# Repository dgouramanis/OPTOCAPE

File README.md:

Photocoupler cape for BeagleBone Black with integrated video serializer

https://youtu.be/7uQYPXgA6WU

This cape was originally designed for a CNC milling machine. The opto-I/O was designed to accomidate four stepper axis with limit switches, spindle, coolant, LED light, and more. 

The UI section of the cape includes a LVDS serializer compatible with many flatscreen LCDs. Four-wire touchscreen is supported.

Features:

    15 high-speed outputs (opto)
    10 high-speed inputs (opto)
    UART TX RX (opto)    
    4 opto relay outputs (500mA)
    12 bit color LVDS video (CMOS)
    4 analog inputs (CMOS)

The outputs are divided into five sections. Each section is powered through seperate V and GND nets. 

The input voltage range is 3-6 volts.

5 VDC power source connected to DC power Jack or VDD_5V is required for LVDS.

You can buy an Optocape at the link below. 

https://www.tindie.com/products/TEMProducts/optocape/

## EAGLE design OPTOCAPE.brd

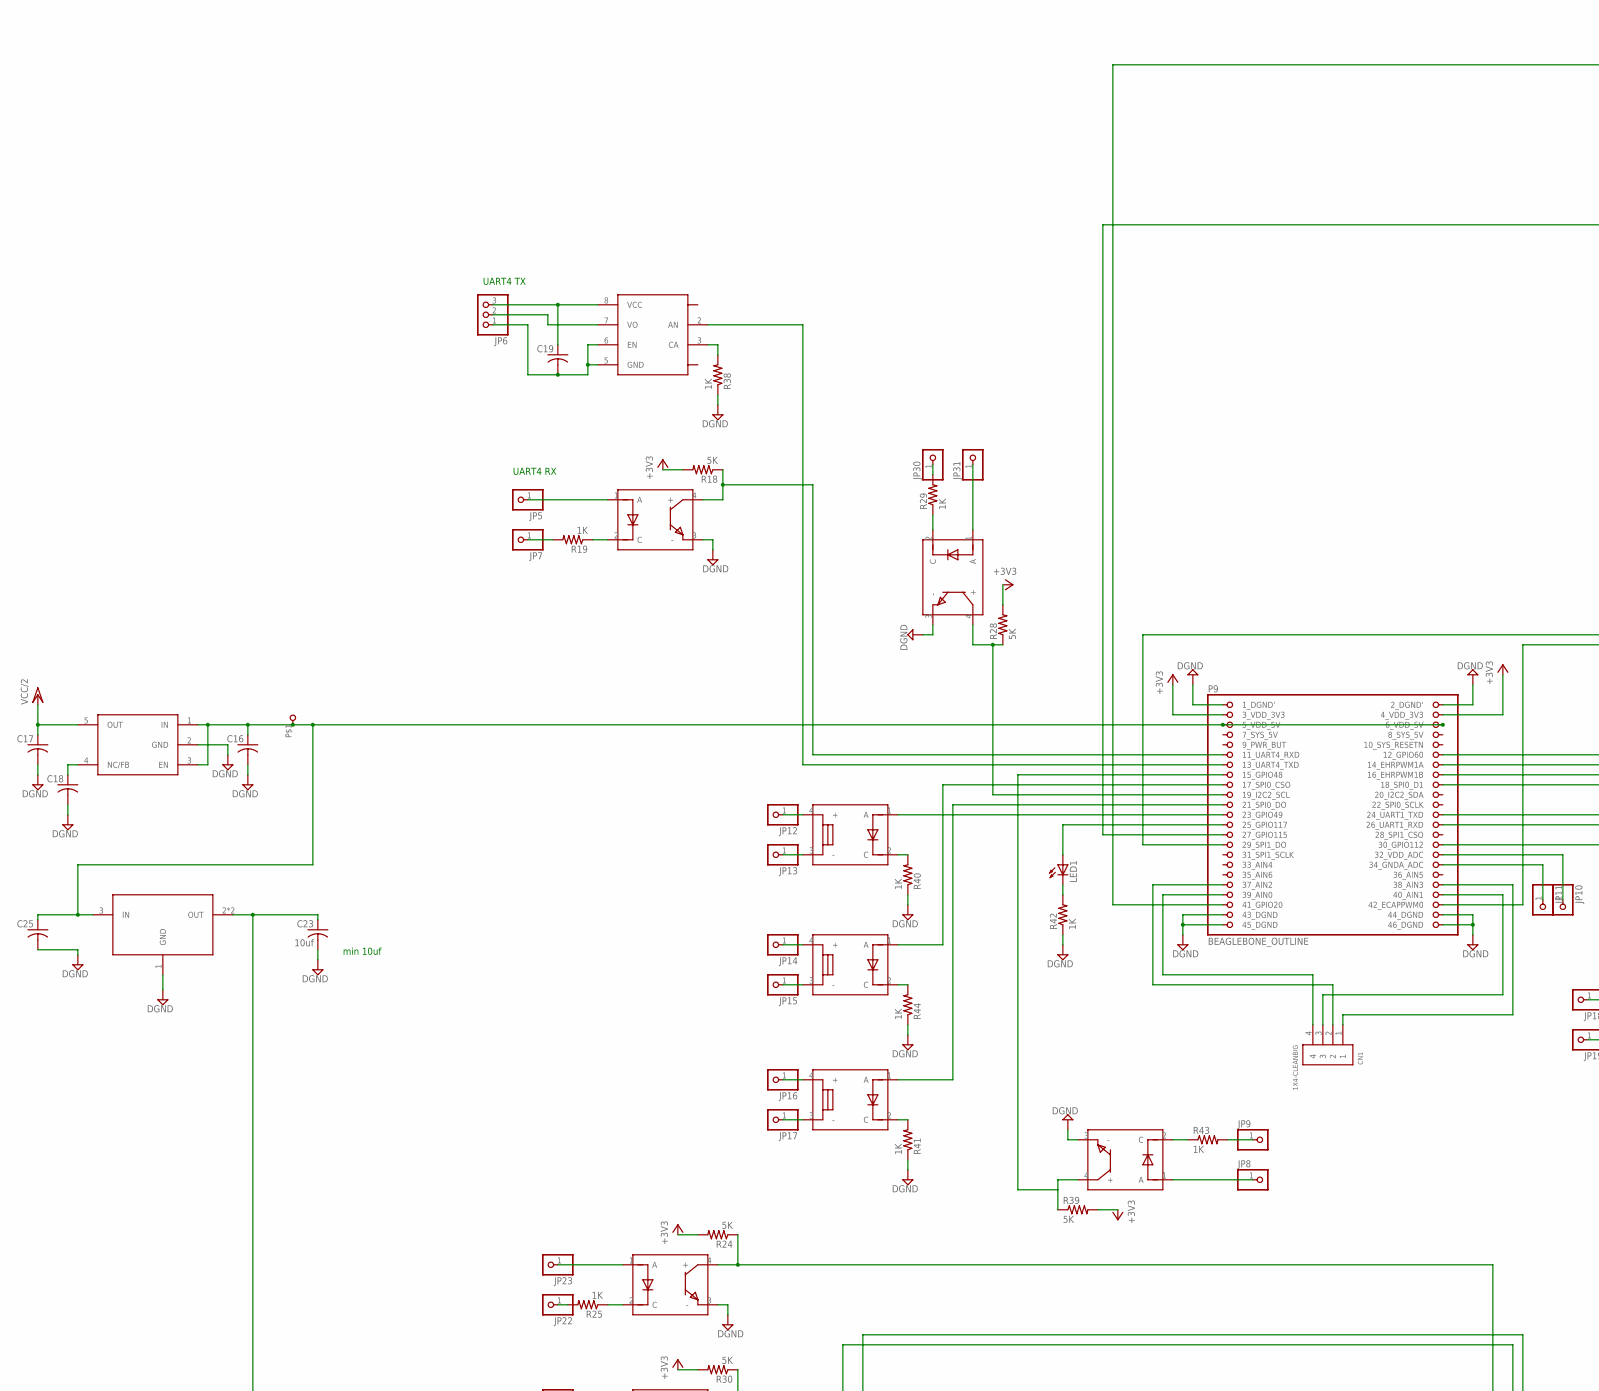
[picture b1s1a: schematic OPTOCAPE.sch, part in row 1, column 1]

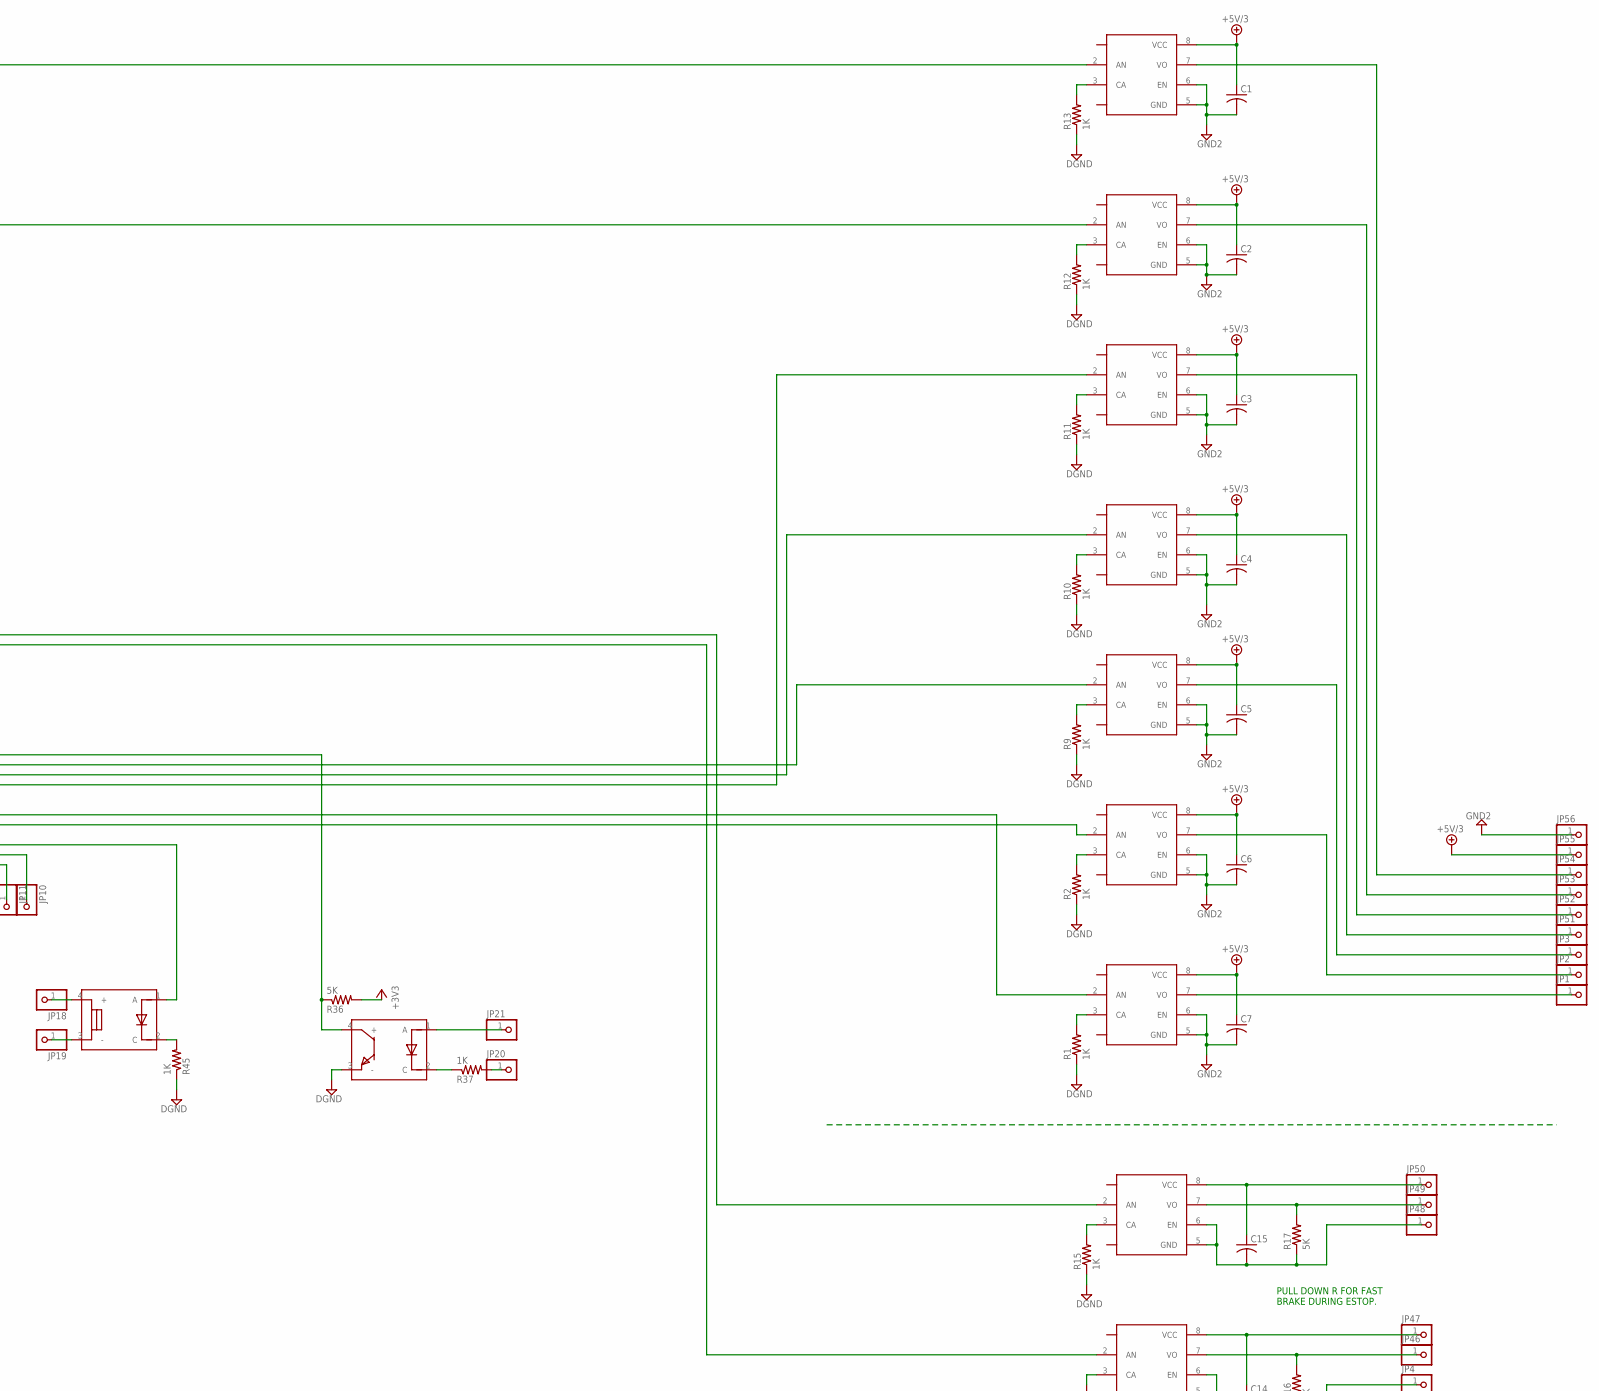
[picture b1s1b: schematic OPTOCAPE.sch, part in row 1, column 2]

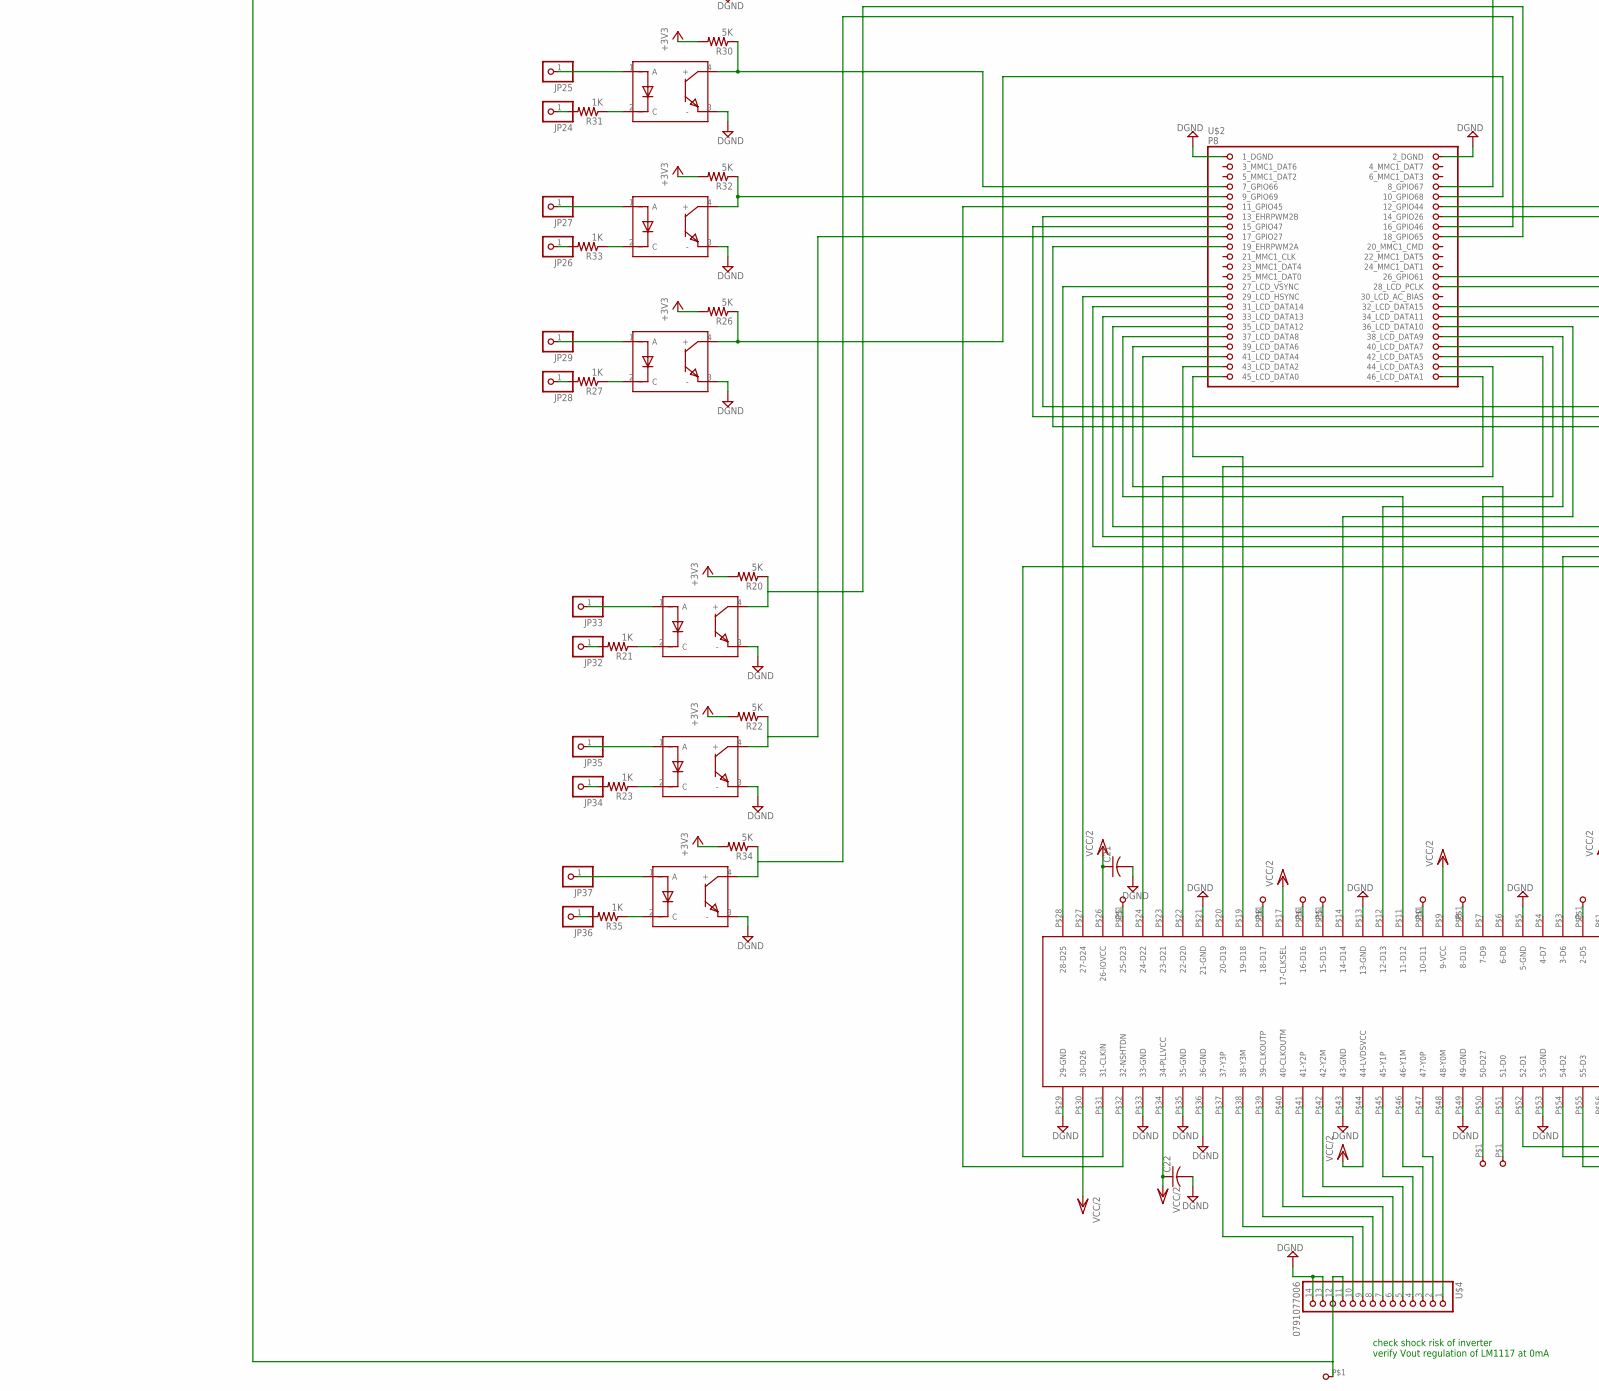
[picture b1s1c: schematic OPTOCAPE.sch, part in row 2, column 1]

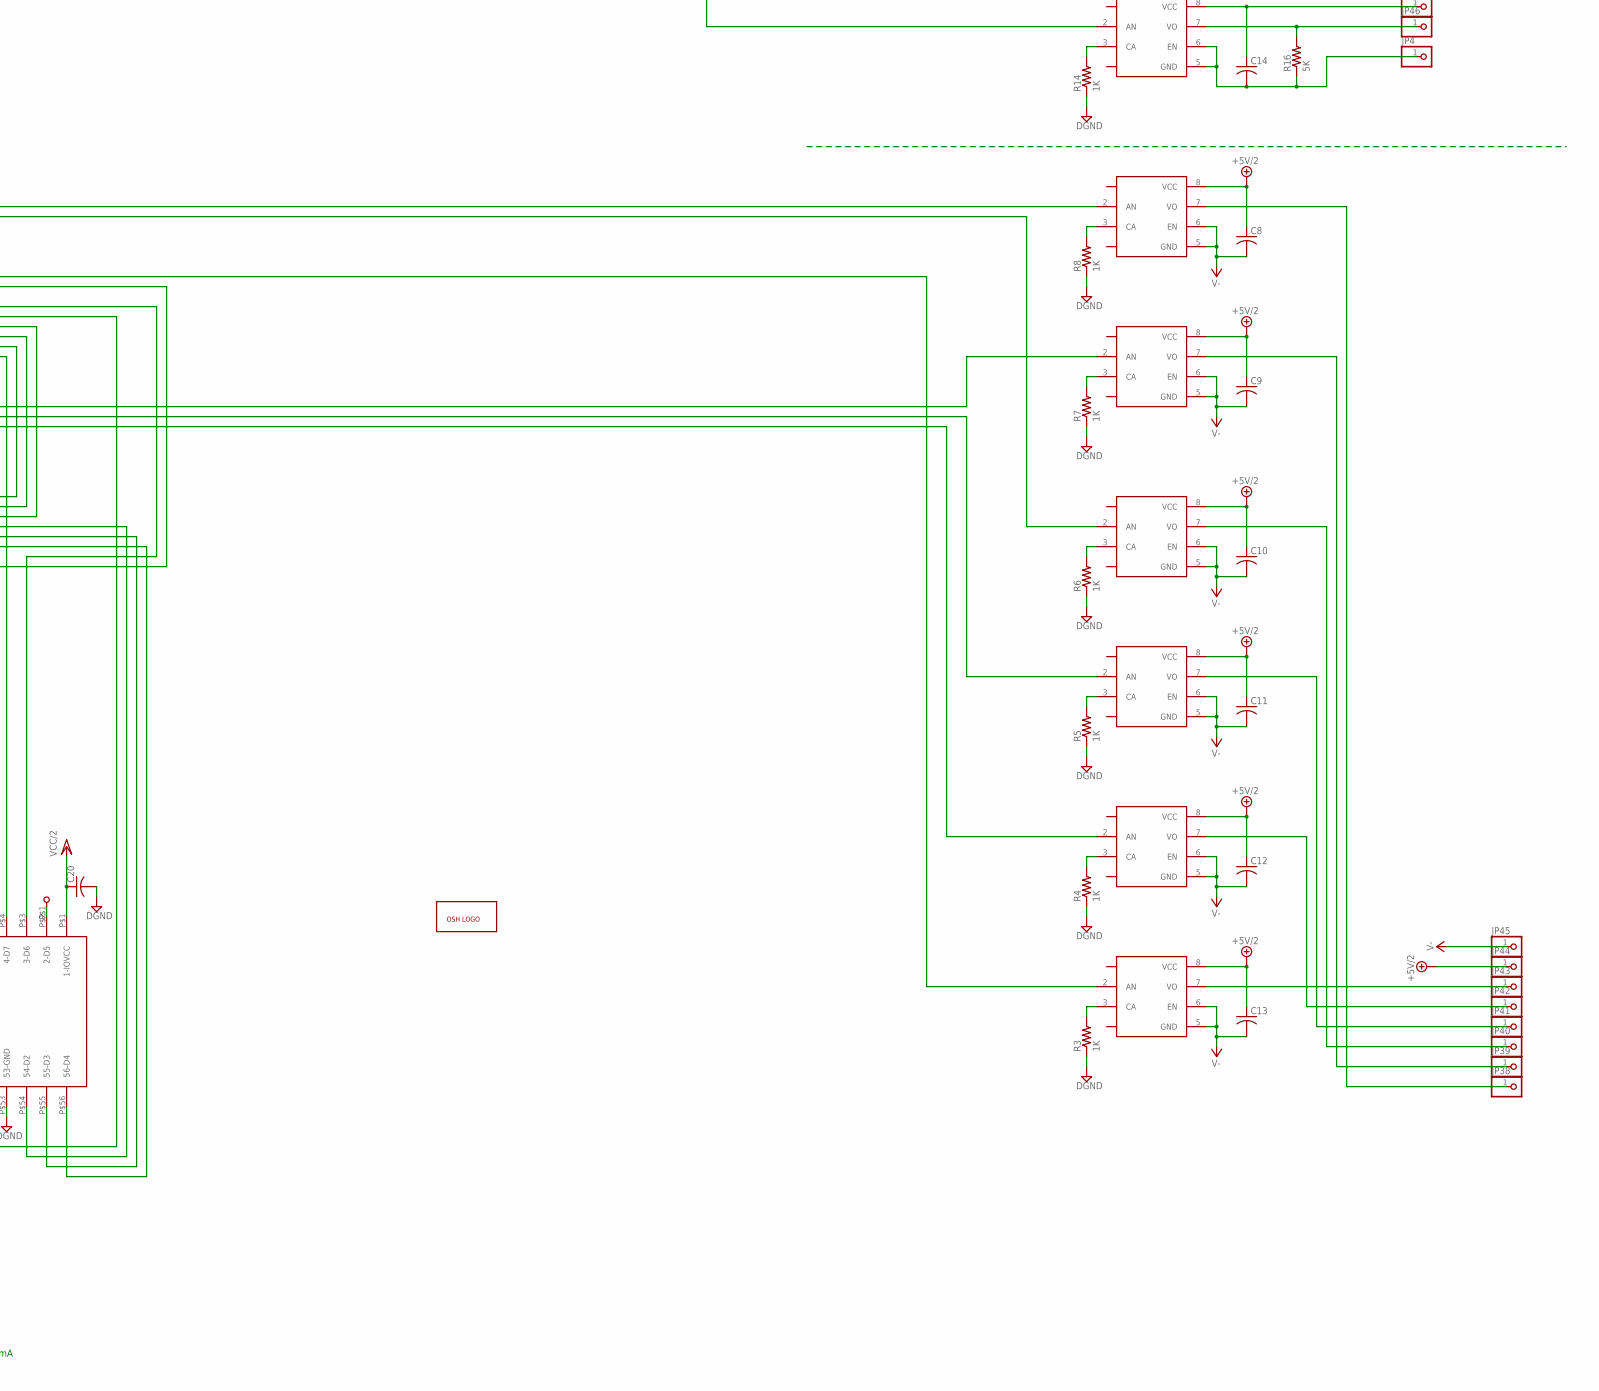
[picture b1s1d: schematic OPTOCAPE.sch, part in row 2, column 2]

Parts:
0000, 8.12, 8.13, 8.14, 8.15, 8.19, 8.26, 9.3, 9.14, 9.16, 9.18, 9.24, 9.26, 9.27, 9.41, 1111: TLP2200F; DIL08-ROUND
C1, C2, C3, C4, C5, C6, C7, C8, C9, C10, C11, C12, C13, C14, C15, C16, C17, C19: C-USC0805K; C0805K
C18, C20, C21, C22, C25: C-USC0402; C0402
C23: 10uf; C0805K
CN1: 1X4-CLEANBIG; 1X04-CLEANBIG
JP1, JP2, JP3, JP4, JP5, JP7, JP8, JP9, JP10, JP11, JP12, JP13, JP14, JP15, JP16, JP17, JP18, JP19, JP20, JP21, JP22, JP23, JP24, JP25, JP26, JP27, JP28, JP29, JP30, JP31, JP32, JP33, JP34, JP35, JP36, JP37, JP38, JP39, JP40, JP41, JP42, JP43, JP44, JP45, JP46, JP47, JP48, JP49, JP50, JP51, JP52, JP53, JP54, JP55, JP56: PINHD-1X1CB; 1X01-CLEANBIG
JP6: PINHD-1X3CB; 1X03-CLEANBIG
LED1: LED5MM
R1, R2, R3, R4, R5, R6, R7, R8, R9, R10, R11, R12, R13, R14, R15, R19, R21, R23, R25, R27, R29, R31, R33, R35, R37, R38, R40, R41, R42, R43, R44, R45: 1K; R0603
R16, R17, R18, R20, R22, R24, R26, R28, R30, R32, R34, R36, R39: 5K; R0603
SPICS1, SPICS2, SPICS3, SPICS4: TLP222A; DIL04-ROUND
TPS73133: TPS76350DBVR; SOT23-5L
U$1, U$6, U$7, U$8, U$9, U$10, U$11, U$12, U$13, U$14, U$15: FOD817B; DIL04-ROUND
U$2: BEAGLEBONE_OUTLINE; BEAGLEBONE_SHIELD
U$3: SN75LVDS83B; DGG0056A
U$4: 0791077006
U$5, U$16, U$19, U$20, U$21, U$22, U$23, U$24, U$25, U$32, U$33: DEAN_SMALL_VIA
U$17: OSH_LOGO
U$18: LM1117; SOT223

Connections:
7_SYS_5V: U$2.53 (7_SYS_5V)
8.7: R30.1, U$2.7 (7_GPIO66), U$12.4 (+)
8.8: R24.1, U$2.8 (8_GPIO67), U$9.4 (+)
8.9: R32.1, U$2.9 (9_GPIO69), U$13.4 (+)
8.10: R26.1, U$2.10 (10_GPIO68), U$10.4 (+)
8.11: U$2.11 (11_GPIO45), U$3.P$32 (32-NSHTDN)
8.12: 8.12.2 (AN), U$2.12 (12_GPIO44)
8.13: 8.13.2 (AN), U$2.13 (13_EHRPWM2B)
8.14: 8.14.2 (AN), U$2.14 (14_GPIO26)
8.15: 8.15.2 (AN), U$2.15 (15_GPIO47)
8.16: R34.1, U$2.16 (16_GPIO46), U$14.4 (+)
8.17: R22.1, U$2.17 (17_GPIO27), U$8.4 (+)
8.18: R20.1, U$2.18 (18_GPIO65), U$7.4 (+)
8.19: 8.19.2 (AN), U$2.19 (19_EHRPWM2A)
8.26: 8.26.2 (AN), U$2.26 (26_GPIO61)
9.11: R18.1, U$2.57 (11_UART4_RXD), U$6.4 (+)
9.12: R36.1, U$2.58 (12_GPIO60), U$15.4 (+)
9.13: 9.3.2 (AN), U$2.59 (13_UART4_TXD)
9.14: 9.14.2 (AN), U$2.60 (14_EHRPWM1A)
9.15: R39.1, U$1.4 (+), U$2.61 (15_GPIO48)
9.16: 9.16.2 (AN), U$2.62 (16_EHRPWM1B)
9.17: SPICS3.1 (A), U$2.63 (17_SPI0_CSO)
9.18: 9.18.2 (AN), U$2.64 (18_SPI0_D1)
9.19: R28.1, U$2.65 (19_I2C2_SCL), U$11.4 (+)
9.21: SPICS2.1 (A), U$2.67 (21_SPI0_DO)
9.23: SPICS1.1 (A), U$2.69 (23_GPIO49)
9.24: 9.24.2 (AN), U$2.70 (24_UART1_TXD)
9.25: LED1.A, U$2.71 (25_GPIO117)
9.26: 9.26.2 (AN), U$2.72 (26_UART1_RXD)
9.27: 9.27.2 (AN), U$2.73 (27_GPIO115)
9.29: 1111.2 (AN), U$2.75 (29_SPI1_DO)
9.30: SPICS4.1 (A), U$2.76 (30_GPIO112)
9.32: JP10.1, U$2.78 (32_VDD_ADC)
9.34: JP11.1, U$2.80 (34_GNDA_ADC)
9.37: CN1.2, U$2.83 (37_AIN2)
9.38: CN1.1, U$2.84 (38_AIN3)
9.39: CN1.4, U$2.85 (39_AIN0)
9.40: CN1.3, U$2.86 (40_AIN1)
9.41: 9.41.2 (AN), U$2.87 (41_GPIO20)
9.42: 0000.2 (AN), U$2.88 (42_ECAPPWM0)
+3V3: R18.2, R20.2, R22.2, R24.2, R26.2, R28.2, R30.2, R32.2, R34.2, R36.2, R39.2, U$2.49 (3_VDD_3V3), U$2.50 (4_VDD_3V3)
+5V/2: 8.12.8 (VCC), 8.13.8 (VCC), 8.14.8 (VCC), 8.15.8 (VCC), 8.19.8 (VCC), 8.26.8 (VCC), C8.1, C9.1, C10.1, C11.1, C12.1, C13.1, JP44.1
DGND: C16.2, C17.2, C18.2, C20.2, C21.2, C22.2, C23.2, C25.2, R1.1, R2.1, R3.1, R4.1, R5.1, R6.1, R7.1, R8.1, R9.1, R10.1, R11.1, R12.1, R13.1, R14.1, R15.1, R38.1, R40.1, R41.1, R42.1, R44.1, R45.1, TPS73133.2 (GND), U$1.3 (-), U$2.1 (1_DGND), U$2.2 (2_DGND), U$2.47 (1_DGND'), U$2.48 (2_DGND'), U$2.89 (43_DGND), U$2.90 (44_DGND), U$2.91 (45_DGND), U$2.92 (46_DGND), U$3.P$5 (5-GND), U$3.P$13 (13-GND), U$3.P$21 (21-GND), U$3.P$29 (29-GND), U$3.P$33 (33-GND), U$3.P$35 (35-GND), U$3.P$36 (36-GND), U$3.P$43 (43-GND), U$3.P$49 (49-GND), U$3.P$53 (53-GND), U$4.13, U$4.14, U$6.3 (-), U$7.3 (-), U$8.3 (-), U$9.3 (-), U$10.3 (-), U$11.3 (-), U$12.3 (-), U$13.3 (-), U$14.3 (-), U$15.3 (-), U$18.1 (GND)
GND2: 9.14.5 (GND), 9.14.6 (EN), 9.16.5 (GND), 9.16.6 (EN), 9.18.5 (GND), 9.18.6 (EN), 9.24.5 (GND), 9.24.6 (EN), 9.26.5 (GND), 9.26.6 (EN), 9.27.5 (GND), 9.27.6 (EN), 9.41.5 (GND), 9.41.6 (EN), C1.2, C2.2, C3.2, C4.2, C5.2, C6.2, C7.2, JP56.1
HSYNC: U$2.29 (29_LCD_HSYNC), U$3.P$27 (27-D24)
unnamed: 9.24.3 (CA), R1.2
unnamed: C23.1, U$4.11, U$4.12, U$5.P$1, U$18.2 (OUT), U$18.TAB (OUT)
unnamed: 9.26.3 (CA), R2.2
unnamed: 8.26.3 (CA), R3.2
unnamed: 8.19.3 (CA), R4.2
unnamed: 8.15.3 (CA), R5.2
unnamed: 8.14.3 (CA), R6.2
unnamed: 8.13.3 (CA), R7.2
unnamed: 8.12.3 (CA), R8.2
unnamed: 9.26.7 (VO), JP2.1
unnamed: 9.14.3 (CA), R9.2
unnamed: 9.24.7 (VO), JP1.1
unnamed: 9.16.3 (CA), R10.2
unnamed: 9.18.3 (CA), R11.2
unnamed: C18.1, TPS73133.4 (NC/FB)
unnamed: 9.27.3 (CA), R12.2
unnamed: 9.41.3 (CA), R13.2
unnamed: 0000.3 (CA), R14.2
unnamed: 1111.3 (CA), R15.2
unnamed: 0000.5 (GND), 0000.6 (EN), C14.2, JP4.1, R16.1
unnamed: 1111.5 (GND), 1111.6 (EN), C15.2, JP48.1, R17.1
unnamed: 9.14.7 (VO), JP3.1
unnamed: 9.16.7 (VO), JP51.1
unnamed: 9.18.7 (VO), JP52.1
unnamed: 9.27.7 (VO), JP53.1
unnamed: 9.41.7 (VO), JP54.1
unnamed: 0000.8 (VCC), C14.1, JP47.1
unnamed: 1111.8 (VCC), C15.1, JP50.1
unnamed: 1111.7 (VO), JP49.1, R17.2
unnamed: 0000.7 (VO), JP46.1, R16.2
unnamed: 8.12.7 (VO), JP38.1
unnamed: 8.13.7 (VO), JP39.1
unnamed: 8.14.7 (VO), JP40.1
unnamed: 8.15.7 (VO), JP41.1
unnamed: 8.19.7 (VO), JP42.1
unnamed: 8.26.7 (VO), JP43.1
unnamed: U$2.45 (45_LCD_DATA0), U$3.P$19 (19-D18)
unnamed: U$2.46 (46_LCD_DATA1), U$3.P$20 (20-D19)
unnamed: U$2.43 (43_LCD_DATA2), U$3.P$22 (22-D20)
unnamed: U$2.44 (44_LCD_DATA3), U$3.P$23 (23-D21)
unnamed: U$2.41 (41_LCD_DATA4), U$3.P$24 (24-D22)
unnamed: U$2.42 (42_LCD_DATA5), U$3.P$4 (4-D7)
unnamed: U$2.39 (39_LCD_DATA6), U$3.P$6 (6-D8)
unnamed: U$2.40 (40_LCD_DATA7), U$3.P$7 (7-D9)
unnamed: U$2.37 (37_LCD_DATA8), U$3.P$11 (11-D12)
unnamed: U$2.38 (38_LCD_DATA9), U$3.P$12 (12-D13)
unnamed: U$2.36 (36_LCD_DATA10), U$3.P$14 (14-D14)
unnamed: U$2.34 (34_LCD_DATA11), U$3.P$52 (52-D1)
unnamed: U$2.35 (35_LCD_DATA12), U$3.P$54 (54-D2)
unnamed: U$2.33 (33_LCD_DATA13), U$3.P$55 (55-D3)
unnamed: U$2.31 (31_LCD_DATA14), U$3.P$56 (56-D4)
unnamed: U$2.32 (32_LCD_DATA15), U$3.P$3 (3-D6)
unnamed: U$3.P$2 (2-D5), U$19.P$1
unnamed: U$3.P$50 (50-D27), U$20.P$1
unnamed: U$3.P$8 (8-D10), U$21.P$1
unnamed: U$3.P$10 (10-D11), U$22.P$1
unnamed: U$3.P$16 (16-D16), U$23.P$1
unnamed: U$3.P$18 (18-D17), U$24.P$1
unnamed: U$3.P$25 (25-D23), U$25.P$1
unnamed: JP12.1, SPICS1.4 (+)
unnamed: U$3.P$48 (48-Y0M), U$4.1
unnamed: U$3.P$47 (47-Y0P), U$4.2
unnamed: U$3.P$46 (46-Y1M), U$4.3
unnamed: U$3.P$45 (45-Y1P), U$4.4
unnamed: U$3.P$42 (42-Y2M), U$4.5
unnamed: U$3.P$41 (41-Y2P), U$4.6
unnamed: U$3.P$40 (40-CLKOUTM), U$4.7
unnamed: U$3.P$39 (39-CLKOUTP), U$4.8
unnamed: U$3.P$38 (38-Y3M), U$4.9
unnamed: U$3.P$37 (37-Y3P), U$4.10
unnamed: JP21.1, U$15.1 (A)
unnamed: R19.1, U$6.2 (C)
unnamed: U$3.P$51 (51-D0), U$32.P$1
unnamed: U$3.P$15 (15-D15), U$33.P$1
unnamed: JP13.1, SPICS1.3 (-)
unnamed: JP14.1, SPICS3.4 (+)
unnamed: JP15.1, SPICS3.3 (-)
unnamed: C16.1, C25.1, TPS73133.1 (IN), TPS73133.3 (EN), U$2.51 (5_VDD_5V), U$2.52 (6_VDD_5V), U$16.P$1, U$18.3 (IN)
unnamed: R21.1, U$7.2 (C)
unnamed: R23.1, U$8.2 (C)
unnamed: R25.1, U$9.2 (C)
unnamed: R45.2, SPICS4.2 (C)
unnamed: R27.1, U$10.2 (C)
unnamed: R29.1, U$11.2 (C)
unnamed: R31.1, U$12.2 (C)
unnamed: JP16.1, SPICS2.4 (+)
unnamed: R33.1, U$13.2 (C)
unnamed: R35.1, U$14.2 (C)
unnamed: R37.1, U$15.2 (C)
unnamed: 9.3.3 (CA), R38.2
unnamed: R40.2, SPICS1.2 (C)
unnamed: R41.2, SPICS2.2 (C)
unnamed: LED1.K (C), R42.2
unnamed: 9.3.7 (VO), JP6.2
unnamed: 9.3.5 (GND), 9.3.6 (EN), C19.2, JP6.1
unnamed: JP5.1, U$6.1 (A)
unnamed: JP7.1, R19.2
unnamed: R43.1, U$1.2 (C)
unnamed: JP8.1, U$1.1 (A)
unnamed: JP9.1, R43.2
unnamed: 9.3.8 (VCC), C19.1, JP6.3
unnamed: R44.2, SPICS3.2 (C)
unnamed: JP17.1, SPICS2.3 (-)
unnamed: JP19.1, SPICS4.3 (-)
unnamed: JP18.1, SPICS4.4 (+)
unnamed: JP20.1, R37.2
unnamed: JP36.1, R35.2
unnamed: JP37.1, U$14.1 (A)
unnamed: JP34.1, R23.2
unnamed: JP35.1, U$8.1 (A)
unnamed: JP32.1, R21.2
unnamed: JP33.1, U$7.1 (A)
unnamed: JP30.1, R29.2
unnamed: JP31.1, U$11.1 (A)
unnamed: JP28.1, R27.2
unnamed: JP29.1, U$10.1 (A)
unnamed: JP26.1, R33.2
unnamed: JP27.1, U$13.1 (A)
unnamed: JP24.1, R31.2
unnamed: JP25.1, U$12.1 (A)
unnamed: JP22.1, R25.2
unnamed: JP23.1, U$9.1 (A)
PCLK: U$2.28 (28_LCD_PCLK), U$3.P$31 (31-CLKIN)
V-: 8.12.5 (GND), 8.12.6 (EN), 8.13.5 (GND), 8.13.6 (EN), 8.14.5 (GND), 8.14.6 (EN), 8.15.5 (GND), 8.15.6 (EN), 8.19.5 (GND), 8.19.6 (EN), 8.26.5 (GND), 8.26.6 (EN), C8.2, C9.2, C10.2, C11.2, C12.2, C13.2, JP45.1
VCC/2: C17.1, C20.1, C21.1, C22.1, TPS73133.5 (OUT), U$3.P$1 (1-IOVCC), U$3.P$9 (9-VCC), U$3.P$17 (17-CLKSEL), U$3.P$26 (26-IOVCC), U$3.P$30 (30-D26), U$3.P$34 (34-PLLVCC), U$3.P$44 (44-LVDSVCC)
VSYNC: U$2.27 (27_LCD_VSYNC), U$3.P$28 (28-D25)
XXXXXX: 9.14.8 (VCC), 9.16.8 (VCC), 9.18.8 (VCC), 9.24.8 (VCC), 9.26.8 (VCC), 9.27.8 (VCC), 9.41.8 (VCC), C1.1, C2.1, C3.1, C4.1, C5.1, C6.1, C7.1, JP55.1

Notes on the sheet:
PULL DOWN R FOR FAST BRAKE DURING ESTOP.
UART4 TX
UART4 RX
min 10uf
check shock risk of inverter verify Vout regulation of LM1117 at 0mA

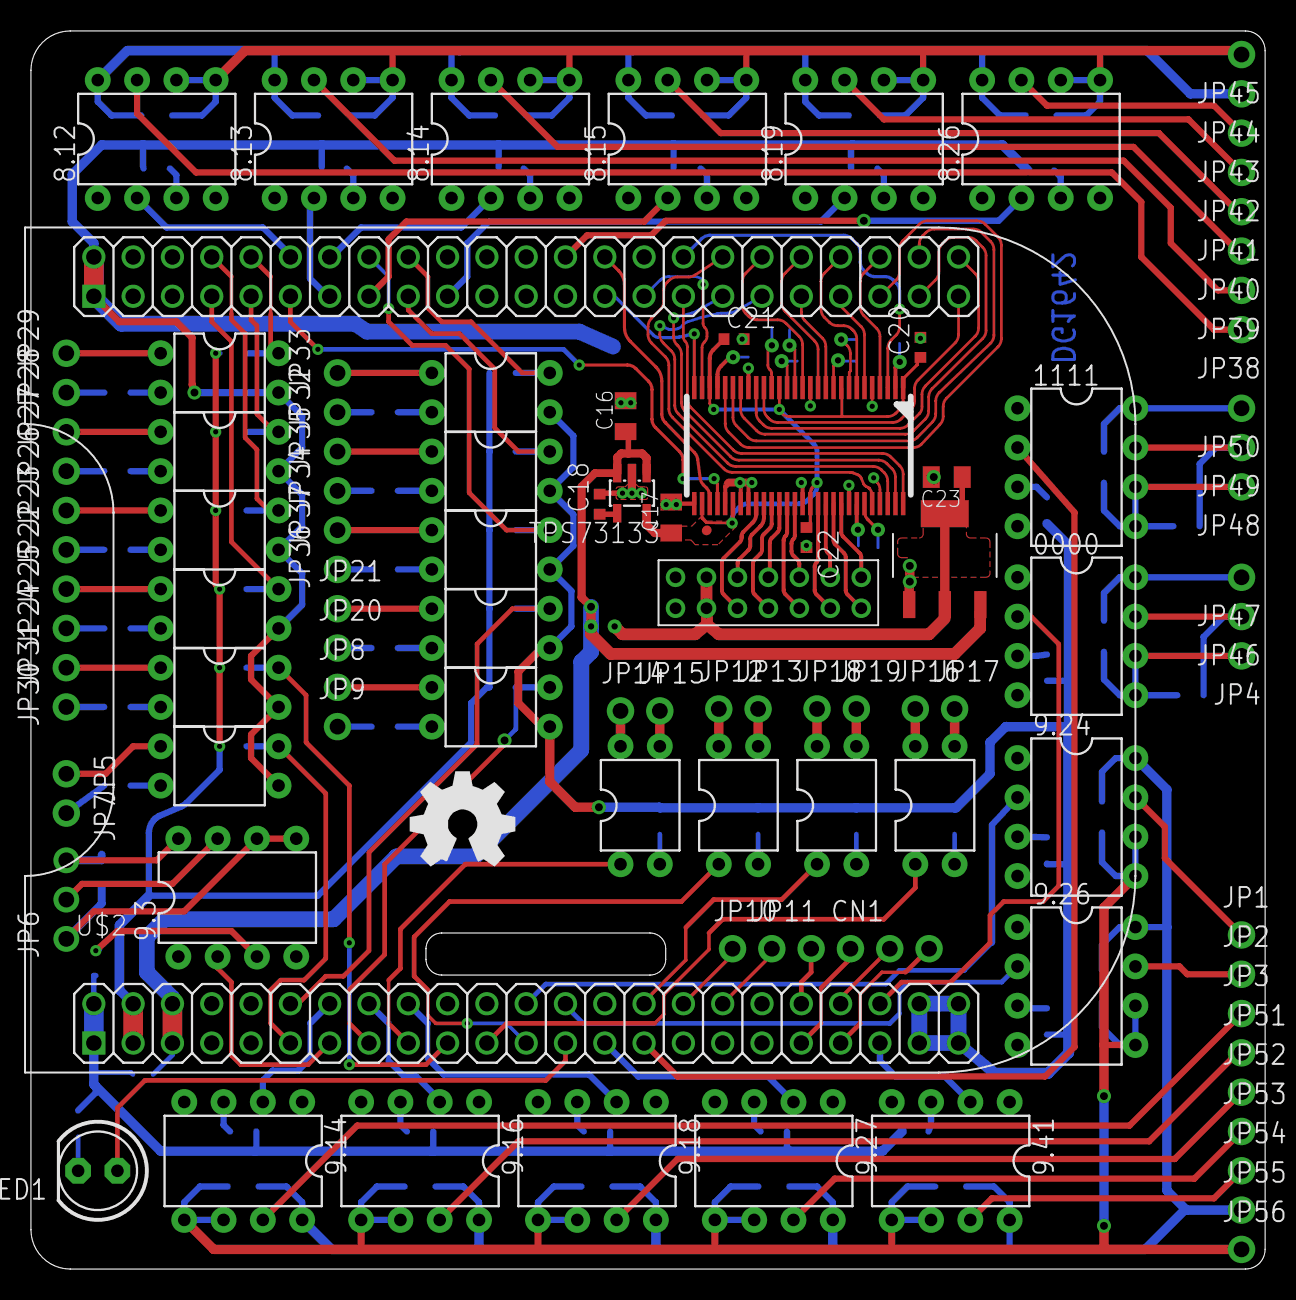
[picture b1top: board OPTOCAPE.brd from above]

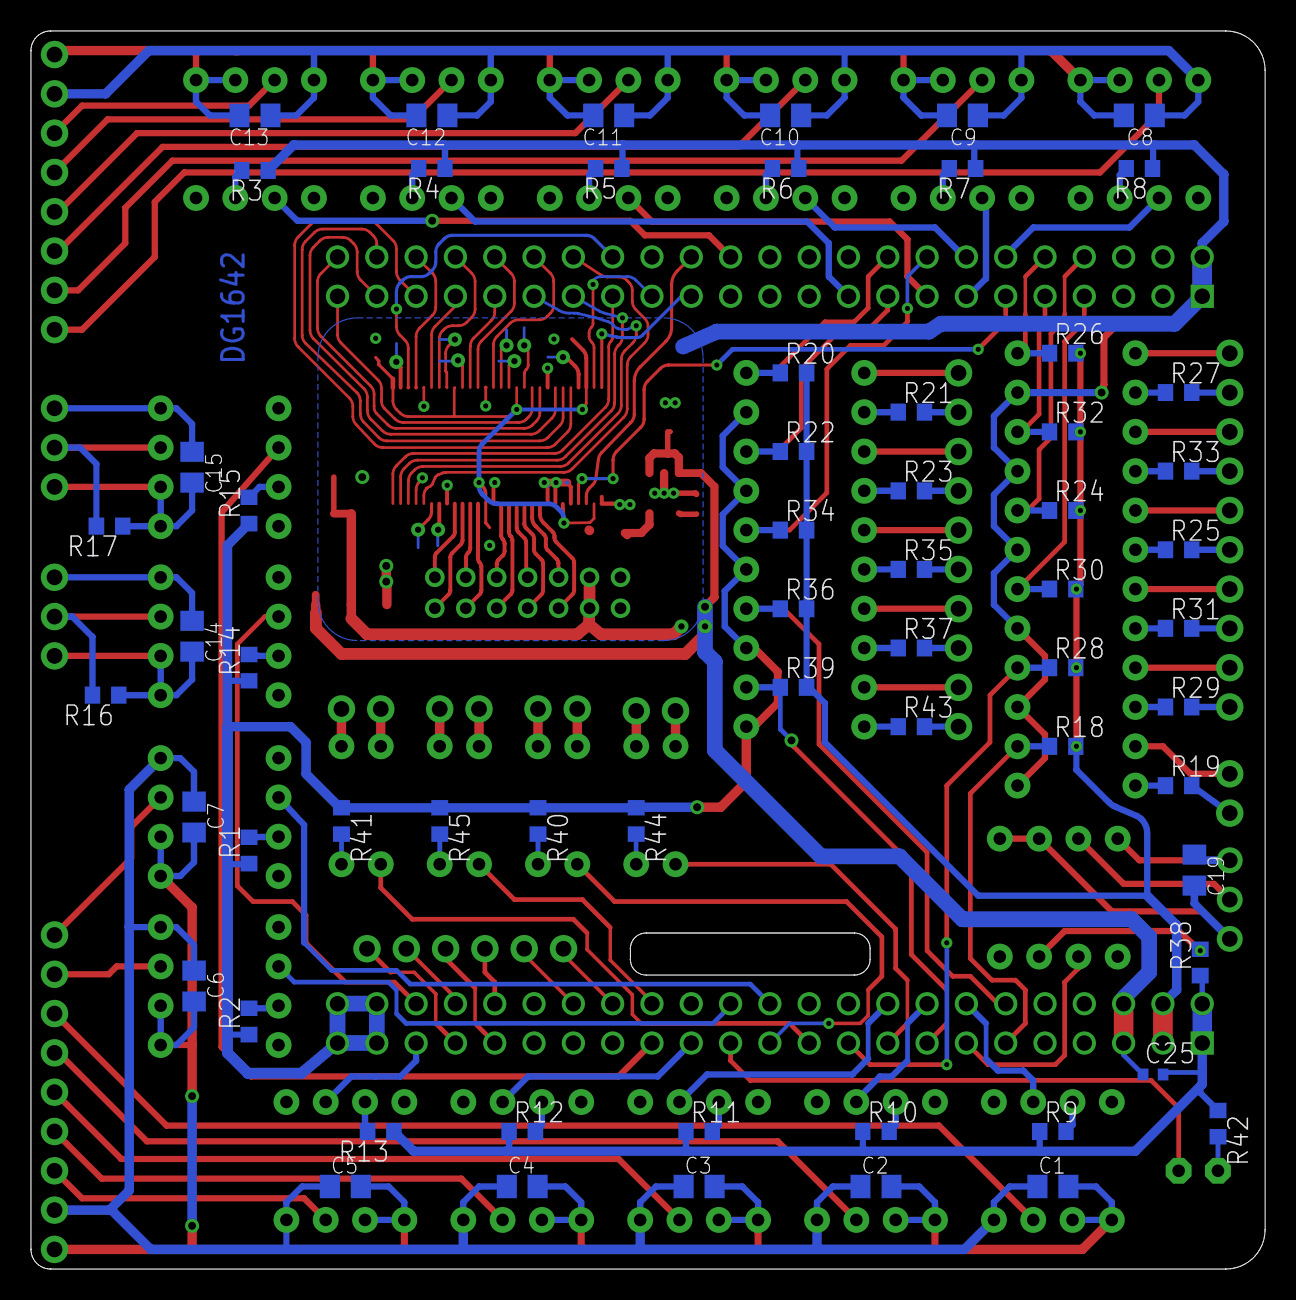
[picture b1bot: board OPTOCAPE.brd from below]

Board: 2 copper layers, 79.8 x 80.0 mm, 175 parts (62 on the bottom side), 171 nets.

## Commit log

2016-10-15 work in progress
2016-10-19 V0.1 Fab version, not yet tested
2016-11-15 V0.1 release
2016-11-15 v0.1
2017-03-05 tested
2017-03-10 developing 3.8x compatible overlay
2017-03-12 debugging 3.8 overlay
2017-03-27 removed UART4 from overlay
2017-04-06 added switch panel controller 0.1
2017-04-16 Create license
2017-10-26 Optocape / BBB Pins compatability spreadsheet
    BBB_Pins spreadsheet www.embedded-things.com including a column for Optocape compatability
2017-10-26 kernel version 4.x
2017-10-26 added readme
2017-12-01 new part numbers
2017-12-09 Update README.md
    added youtube video link
2018-01-25 reference shematic
2018-03-22 Shows a typical cable diagram for LCD display LVDS
